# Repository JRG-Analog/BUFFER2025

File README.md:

# BUFFER2025
A high current open loop buffer
Board is designed to use 40x40x100mm aluminum heatsink, with 40mm square fan for cooling. 

Description: 
The circuit is an open loop buffer, that is, no feedback. Phase shift induced by load impedance does not affect stability. This was originally built to test PSRR on devices which require an input capacitor, but it can be used for many other experiments.

Performance: 
  IOUT +10/-8A normal; +21A/-15A in High Bias
  BW 60MHz, rl = 0.5Ω, 1VRMS, +8V/-3V;
  ZOUT = 250mΩ normal, 25mΩ in High Bias
  Supply Current 45mA normal, 530mA in High Bias

Usage: 
Connect to power supply with current capability to match expected load. The each supply should be set to 3V more than the expected swing. For example, for a 0V to 5V squarewave use +8V and -3V. Connect the input to a function generator. This is high impedance input, so most function generators will have 2x the expected output voltage. Use short heavy cables to conect to the load.

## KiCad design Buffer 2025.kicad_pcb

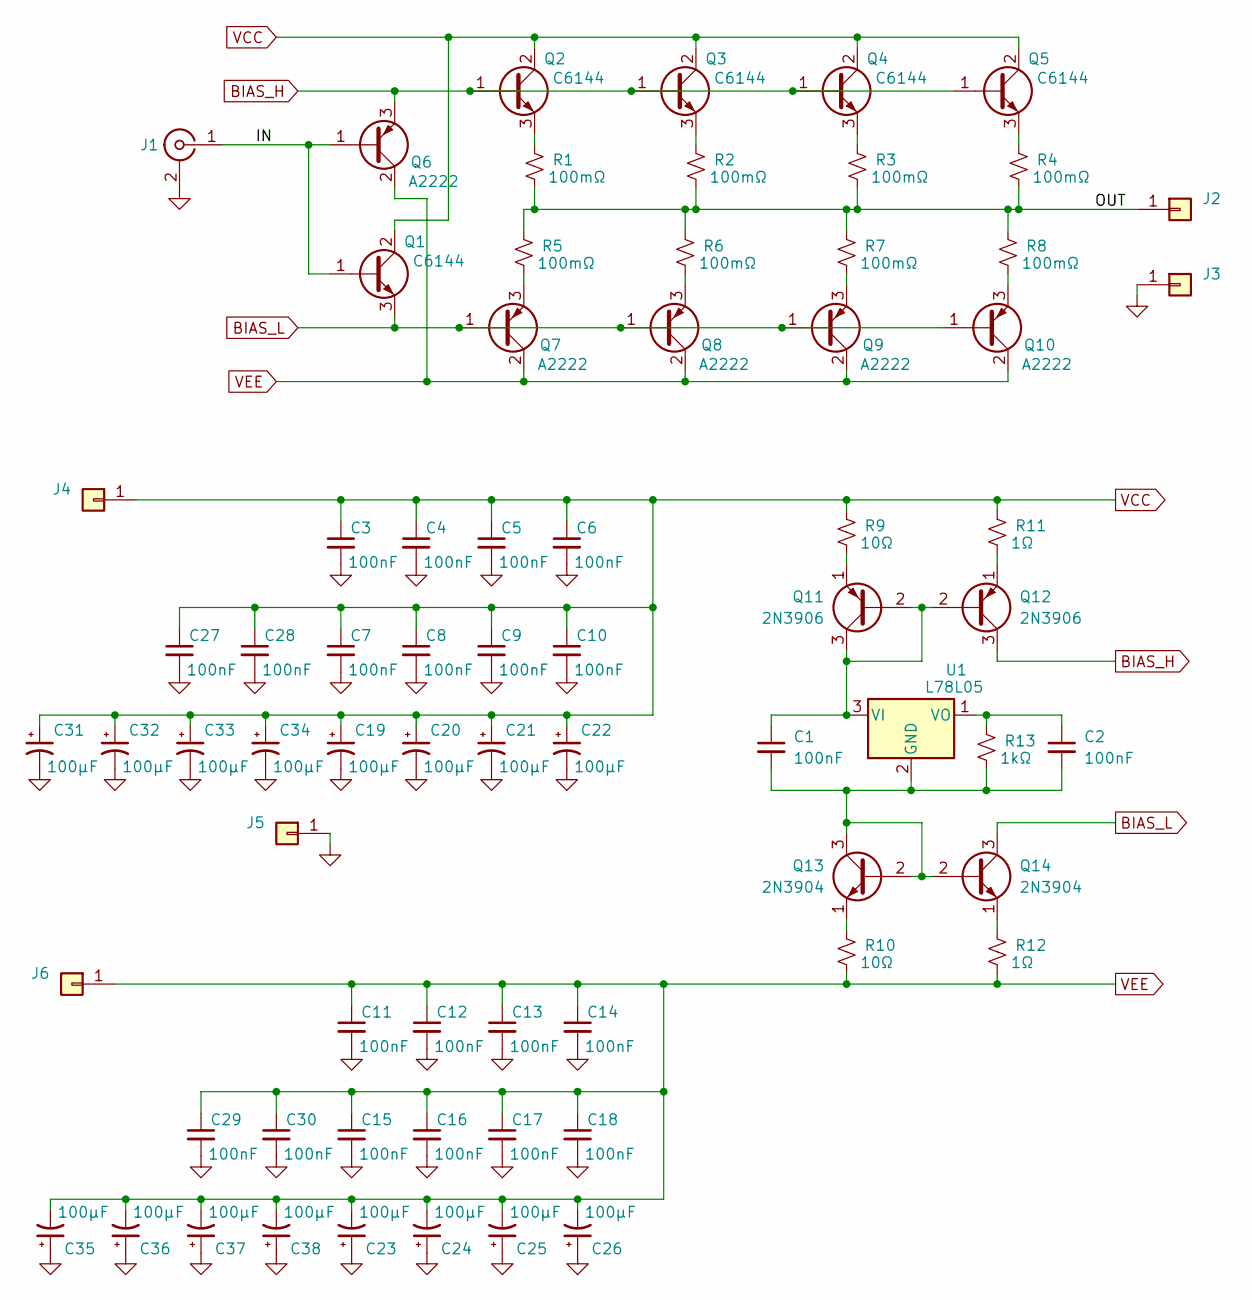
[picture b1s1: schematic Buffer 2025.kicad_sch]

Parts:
C1, C2, C3, C4, C5, C6, C7, C8, C9, C10, C11, C12, C13, C14, C15, C16, C17, C18, C27, C28, C29, C30: 100nF; C_Disc_D4.3mm_W1.9mm_P5.00mm
C19, C20, C21, C22, C23, C24, C25, C26, C31, C32, C33, C34, C35, C36, C37, C38: 100µF; CP_Radial_D6.3mm_P2.50mm
J1: Conn_Coaxial; PinHeader_1x02_P2.54mm_Vertical
J2, J3, J4, J5, J6: TestPoint_Loop_D3.50mm_Drill1.4mm_Beaded
Q1, Q2, Q3, Q4, Q5: C6144; TO-220-3_Vertical_FP
Q6, Q7, Q8, Q9, Q10: A2222; TO-220-3_Vertical_FP
Q11, Q12: 2N3906; TO-92_Inline
Q13, Q14: 2N3904; TO-92_Inline
R1, R2, R3, R4, R5, R6, R7, R8: 100mΩ; R_Axial_DIN0411_L9.9mm_D3.6mm_P12.70mm_Horizontal
R9, R10: 10Ω; R_Axial_DIN0207_L6.3mm_D2.5mm_P7.62mm_Horizontal
R11, R12: 1Ω; R_Axial_DIN0207_L6.3mm_D2.5mm_P7.62mm_Horizontal
R13: 1kΩ; R_Axial_DIN0207_L6.3mm_D2.5mm_P7.62mm_Horizontal
U1: L78L05; TO-92_Inline

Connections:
/IN: J1.1 (In), Q1.1 (B), Q6.1 (B)
/OUT: J2.1, R1.2, R2.2, R3.2, R4.2, R5.1, R6.1, R7.1, R8.1
BIAS_H: Q2.1 (B), Q3.1 (B), Q4.1 (B), Q5.1 (B), Q6.3 (E), Q12.3 (C)
BIAS_L: Q1.3 (E), Q7.1 (B), Q8.1 (B), Q9.1 (B), Q10.1 (B), Q14.3 (C)
GND: C3.2, C4.2, C5.2, C6.2, C7.2, C8.2, C9.2, C10.2, C11.2, C12.2, C13.2, C14.2, C15.2, C16.2, C17.2, C18.2, C19.2, C20.2, C21.2, C22.2, C23.1, C24.1, C25.1, C26.1, C27.2, C28.2, C29.2, C30.2, C31.2, C32.2, C33.2, C34.2, C35.1, C36.1, C37.1, C38.1, J1.2 (Ext), J3.1, J5.1
unnamed: Q2.3 (E), R1.1
unnamed: Q3.3 (E), R2.1
unnamed: Q4.3 (E), R3.1
unnamed: Q5.3 (E), R4.1
unnamed: Q7.3 (E), R5.2
unnamed: Q8.3 (E), R6.2
unnamed: Q9.3 (E), R7.2
unnamed: Q10.3 (E), R8.2
unnamed: C1.1, Q11.2 (B), Q11.3 (C), Q12.2 (B), U1.3 (VI)
unnamed: Q11.1 (E), R9.2
unnamed: Q12.1 (E), R11.2
unnamed: C1.2, C2.2, Q13.2 (B), Q13.3 (C), Q14.2 (B), R13.2, U1.2 (GND)
unnamed: Q13.1 (E), R10.1
unnamed: Q14.1 (E), R12.1
unnamed: C2.1, R13.1, U1.1 (VO)
VCC: C3.1, C4.1, C5.1, C6.1, C7.1, C8.1, C9.1, C10.1, C19.1, C20.1, C21.1, C22.1, C27.1, C28.1, C31.1, C32.1, C33.1, C34.1, J4.1, Q1.2 (C), Q2.2 (C), Q3.2 (C), Q4.2 (C), Q5.2 (C), R9.1, R11.1
VEE: C11.1, C12.1, C13.1, C14.1, C15.1, C16.1, C17.1, C18.1, C23.2, C24.2, C25.2, C26.2, C29.1, C30.1, C35.2, C36.2, C37.2, C38.2, J6.1, Q6.2 (C), Q7.2 (C), Q8.2 (C), Q9.2 (C), Q10.2 (C), R10.2, R12.2

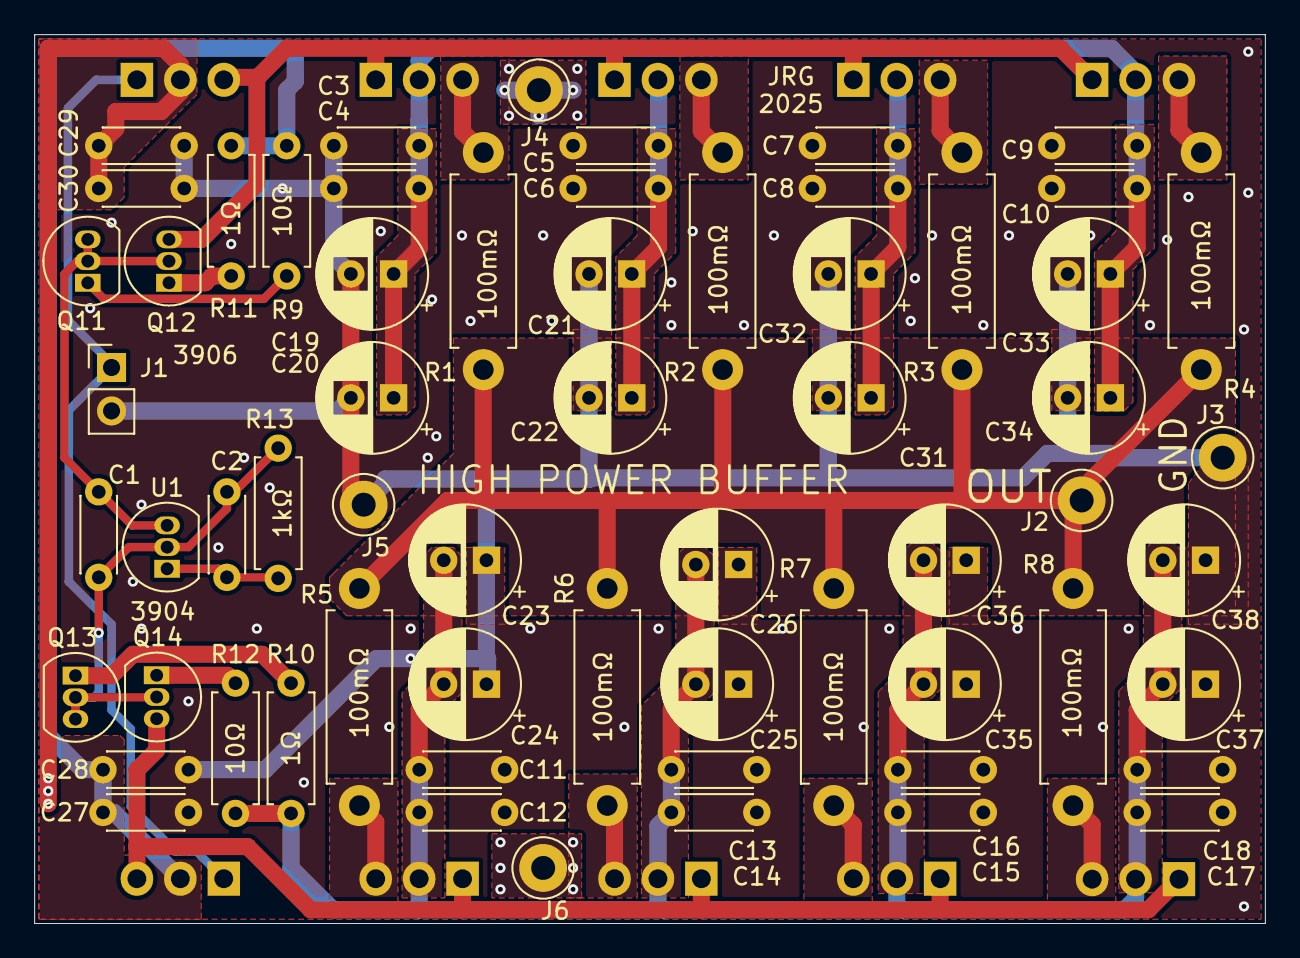
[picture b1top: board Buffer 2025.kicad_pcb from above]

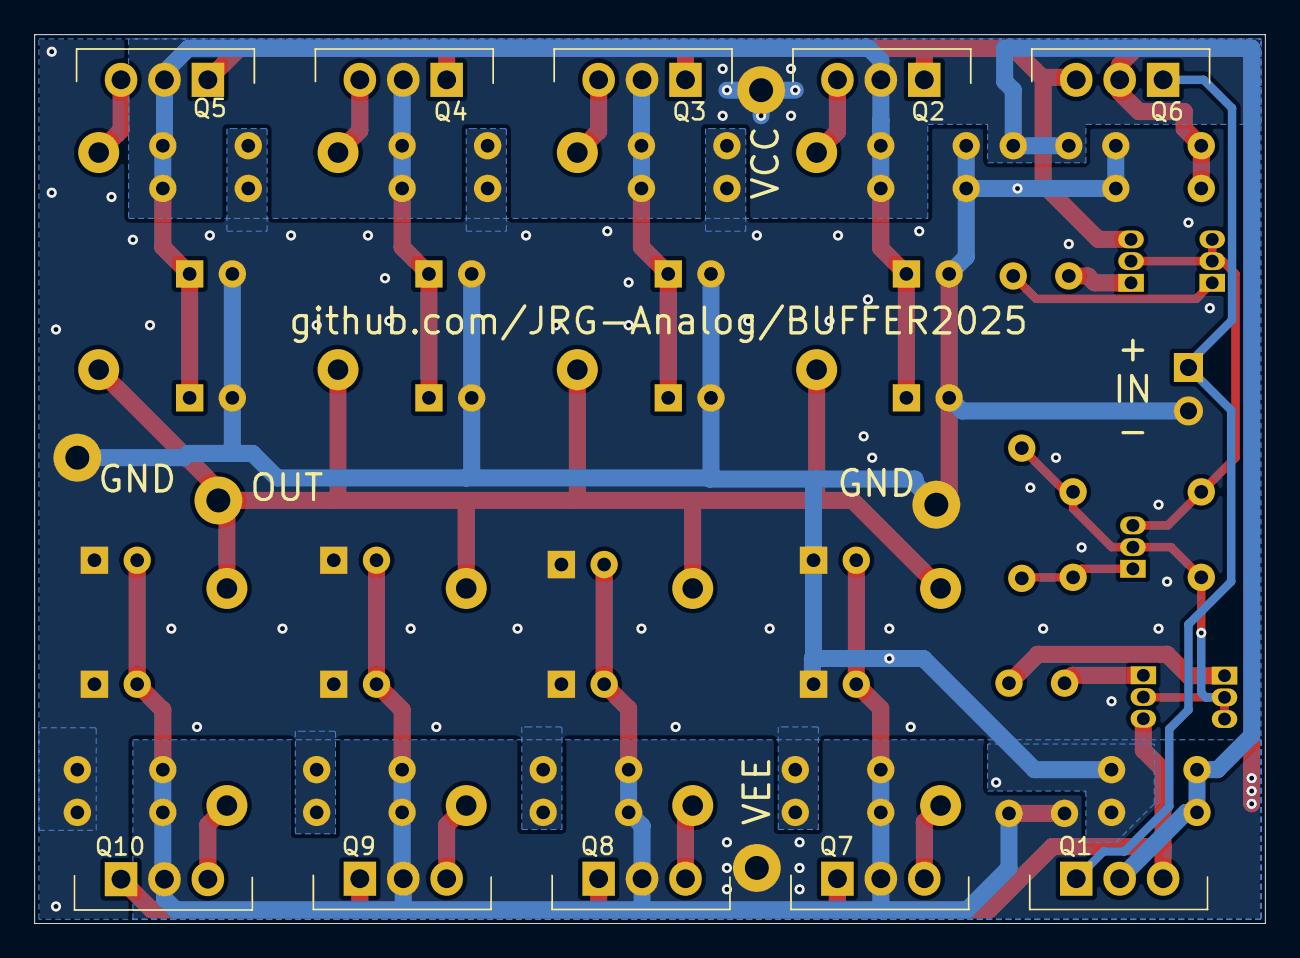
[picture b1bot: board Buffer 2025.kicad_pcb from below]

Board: 2 copper layers, 72.0 x 52.0 mm, 72 parts (10 on the bottom side), 22 nets.
